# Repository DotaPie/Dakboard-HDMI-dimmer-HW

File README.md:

# Dakboard HDMI Dimmer - Hardware

A Raspberry Pi HAT that carries a BH1750 ambient-light sensor and a PIR motion sensor for automatic HDMI display dimming.

Designed for the Raspberry Pi Zero 2 W, but it mounts on any Raspberry Pi with the standard 40-pin header. Pairs with [Dakboard-HDMI-dimmer-FW](https://github.com/DotaPie/Dakboard-HDMI-dimmer-FW), which reads these sensors and adjusts display brightness.

## What's on the board

- **40-pin GPIO header (J1)** - mounts the board as a HAT and breaks out power, I²C, and the PIR line
- **BH1750 light sensor header (J2)** - 5-pin module (VCC / GND / SCL / SDA / ADDR) on I²C bus 1, address `0x23`, with 4K7 pull-ups
- **PIR motion sensor header (J3)** - 3-pin module (VCC / OUT / GND) with the output on GPIO24 (BCM), physical pin 18
- Decoupling and signal-conditioning passives, plus four mounting holes

The BH1750 runs at 3.3 V on the Pi's primary I²C bus; the PIR is powered from 5 V and its output is fed to a GPIO. All dimming logic lives in the firmware - this board just carries the sensors.

## Pin usage

| Signal   | Raspberry Pi pin        | Notes                        |
|----------|-------------------------|------------------------------|
| I²C SDA  | GPIO2 / pin 3           | BH1750 (bus 1, addr `0x23`)  |
| I²C SCL  | GPIO3 / pin 5           | BH1750                       |
| PIR out  | GPIO24 / pin 18         | Motion detection             |
| 3V3      | pin 1                   | BH1750 supply                |
| 5V       | pin 2 / pin 4           | PIR supply                   |
| GND      | pins 6, 9, 14, …        | Common ground                |

## Board specs

- Size: **30 × 65 mm**
- 4× mounting holes
- 2-layer, JLCPCB-ready gerbers included

## Repository layout

```
Dakboard HDMI dimmer KiCAD/
└─ Dakboard HDMI dimmer v1/
   ├─ Dakboard HDMI dimmer v1.kicad_pro   # KiCAD project
   ├─ Dakboard HDMI dimmer v1.kicad_sch   # schematic
   ├─ Dakboard HDMI dimmer v1.kicad_pcb   # PCB layout
   └─ gerber_to_order/                    # zipped gerbers for JLCPCB
```

## Manufacturing

The gerber archive in `gerber_to_order/` is ready to upload to [JLCPCB](https://jlcpcb.com/) (or any fabricator) as-is. To modify the design, open the project in [KiCAD](https://www.kicad.org/) 7 or newer.

## Below is an example of full HW installation with custom cabling

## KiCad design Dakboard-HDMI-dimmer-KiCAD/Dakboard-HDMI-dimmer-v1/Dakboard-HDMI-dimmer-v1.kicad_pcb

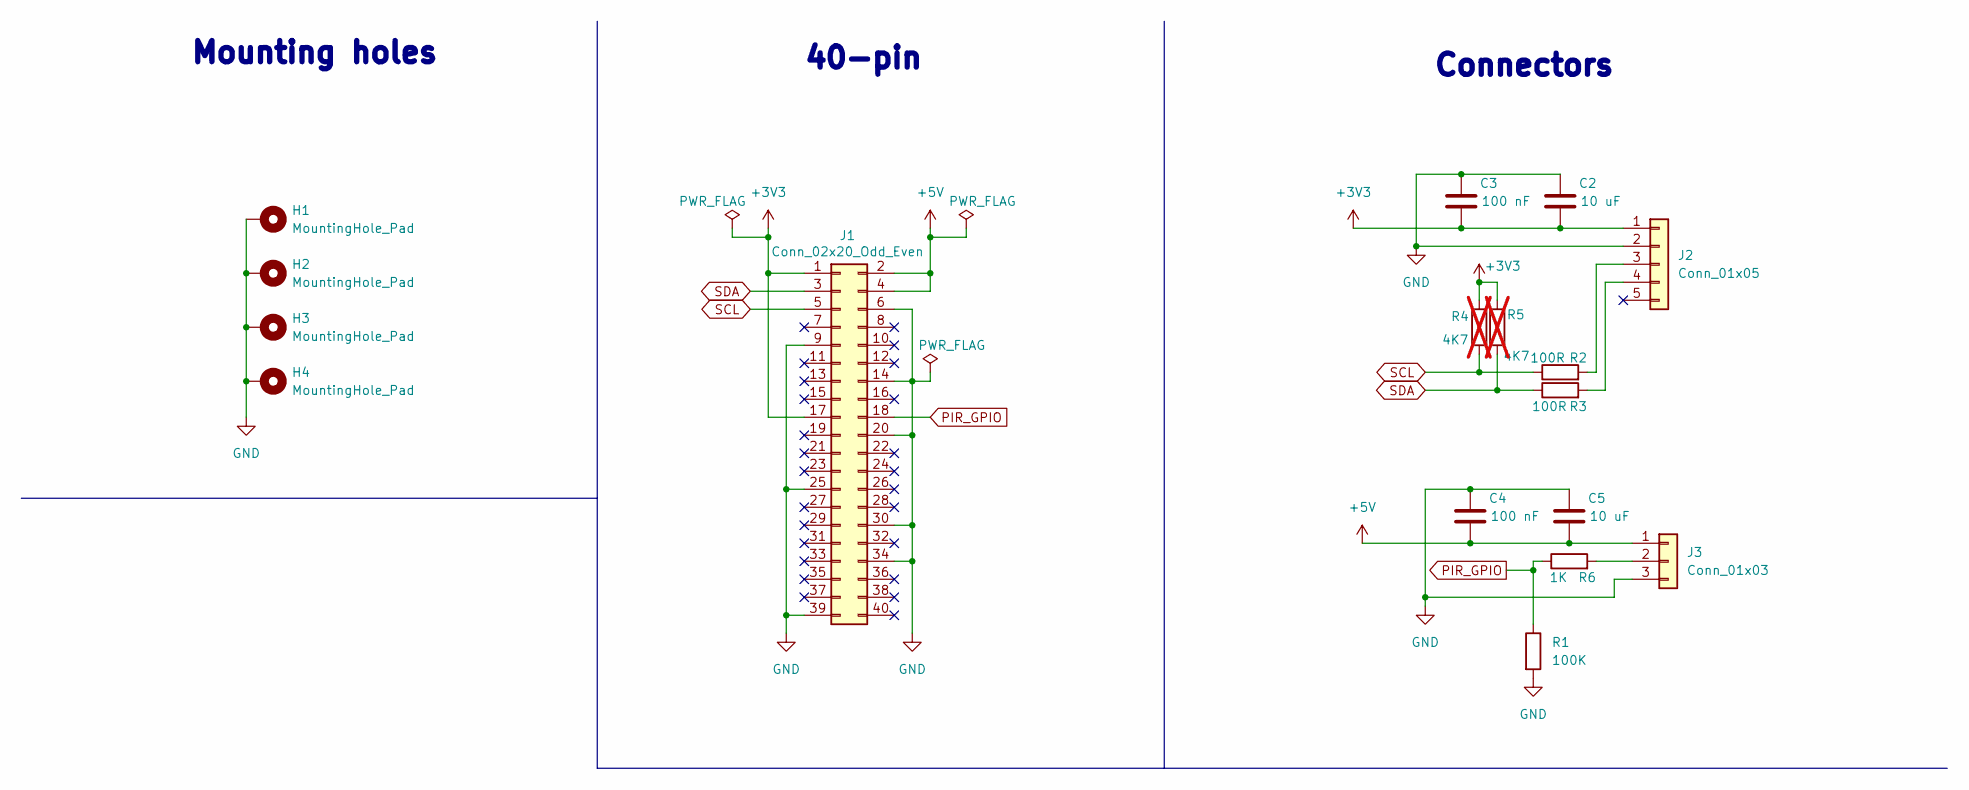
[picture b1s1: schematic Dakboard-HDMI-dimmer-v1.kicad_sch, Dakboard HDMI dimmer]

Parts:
C2, C5: 10 uF; C_0805_2012Metric_Pad1.18x1.45mm_HandSolder
C3, C4: 100 nF; C_0805_2012Metric_Pad1.18x1.45mm_HandSolder
H1, H2, H3, H4: MountingHole_Pad; MountingHole_2.5mm_Pad
J1: Conn_02x20_Odd_Even; PinSocket_2x20_P2.54mm_Vertical
J2: Conn_01x05; PinHeader_1x05_P2.54mm_Horizontal
J3: Conn_01x03; PinHeader_1x03_P2.54mm_Horizontal
R1: 100K; R_0805_2012Metric_Pad1.20x1.40mm_HandSolder
R2, R3: 100R; R_0805_2012Metric_Pad1.20x1.40mm_HandSolder
R4, R5: 4K7; R_0805_2012Metric_Pad1.20x1.40mm_HandSolder; not fitted
R6: 1K; R_0805_2012Metric_Pad1.20x1.40mm_HandSolder

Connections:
+3V3: C2.2, C3.2, J1.1, J1.17, J2.1, R4.1, R5.1
+5V: C4.2, C5.2, J1.2, J1.4, J3.1
GND: C2.1, C3.1, C4.1, C5.1, H1.1 (1_1), H2.1 (1_1), H3.1 (1_1), H4.1 (1_1), J1.6, J1.9, J1.14, J1.20, J1.25, J1.30, J1.34, J1.39, J2.2, J3.3, R1.2
unnamed: J2.3, R2.2
unnamed: J2.4, R3.2
unnamed: J3.2, R6.2
PIR_GPIO: J1.18, R1.1, R6.1
SCL: J1.5, R2.1, R4.2
SDA: J1.3, R3.1, R5.2

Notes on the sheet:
Mounting holes
40-pin
Connectors

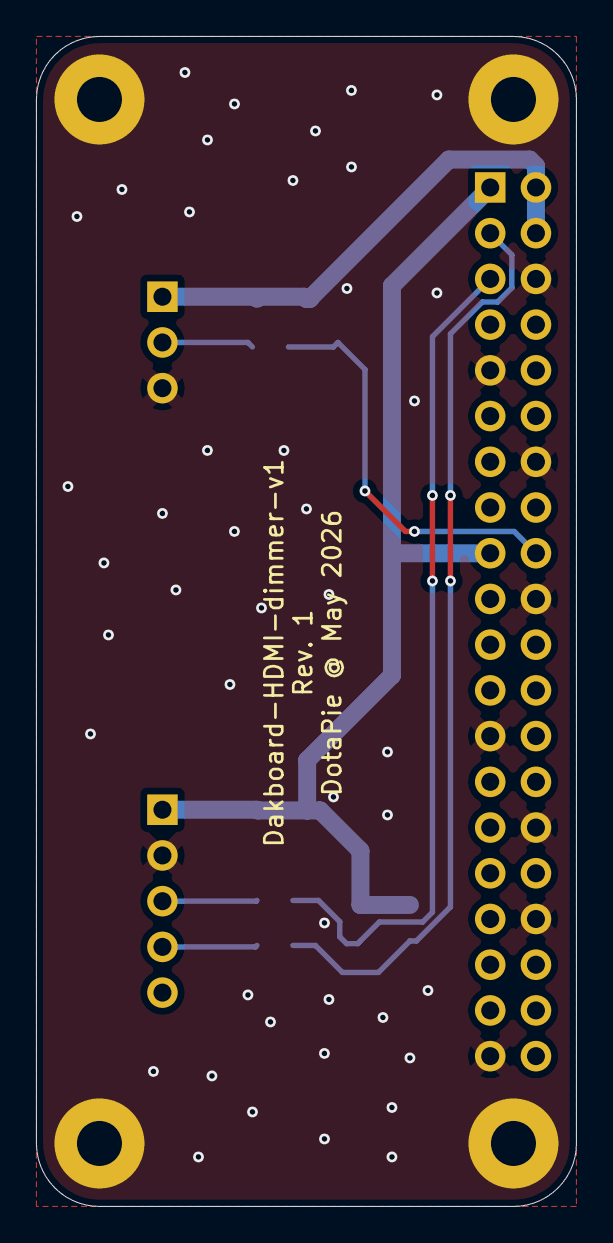
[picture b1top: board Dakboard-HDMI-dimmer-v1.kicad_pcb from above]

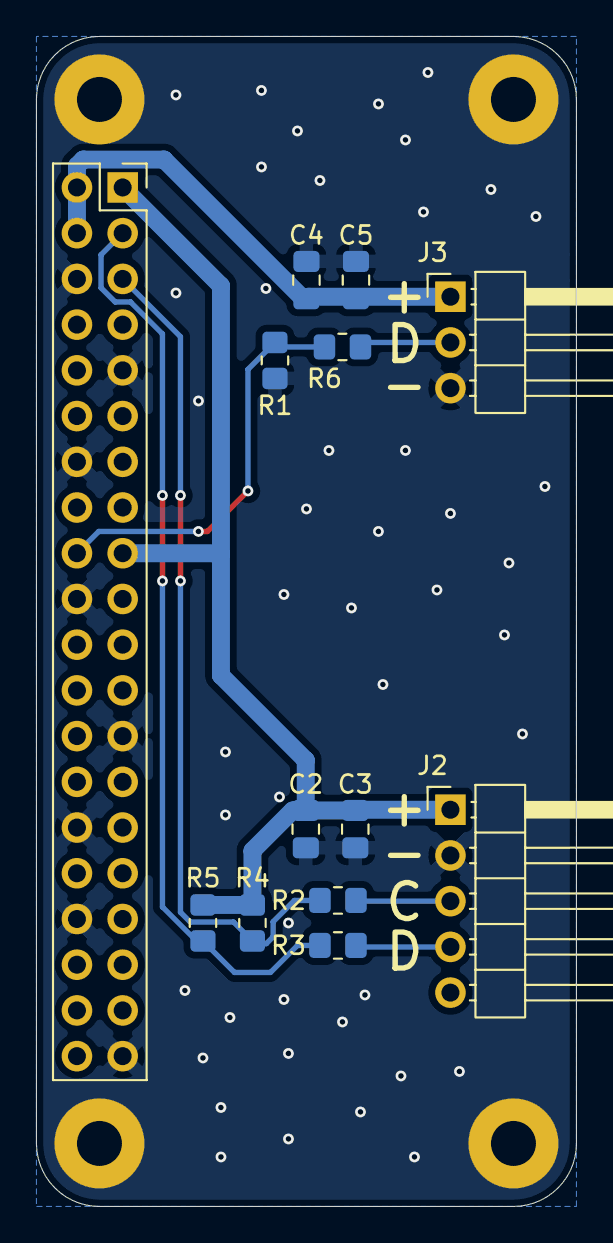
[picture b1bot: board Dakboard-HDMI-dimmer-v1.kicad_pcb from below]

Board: 2 copper layers, 30.0 x 65.0 mm, 17 parts (13 on the bottom side), 9 nets.

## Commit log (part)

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2026-05-10 init
2026-05-10 Init project
2026-05-10 Fixed path
2026-05-10 gitignore fix
2026-05-16 schematic, BOM, board wip
2026-05-16 Board routing, cleanup, jlcpcb export
2026-06-02 Changed R I2C protective to 100R (was 47R)
